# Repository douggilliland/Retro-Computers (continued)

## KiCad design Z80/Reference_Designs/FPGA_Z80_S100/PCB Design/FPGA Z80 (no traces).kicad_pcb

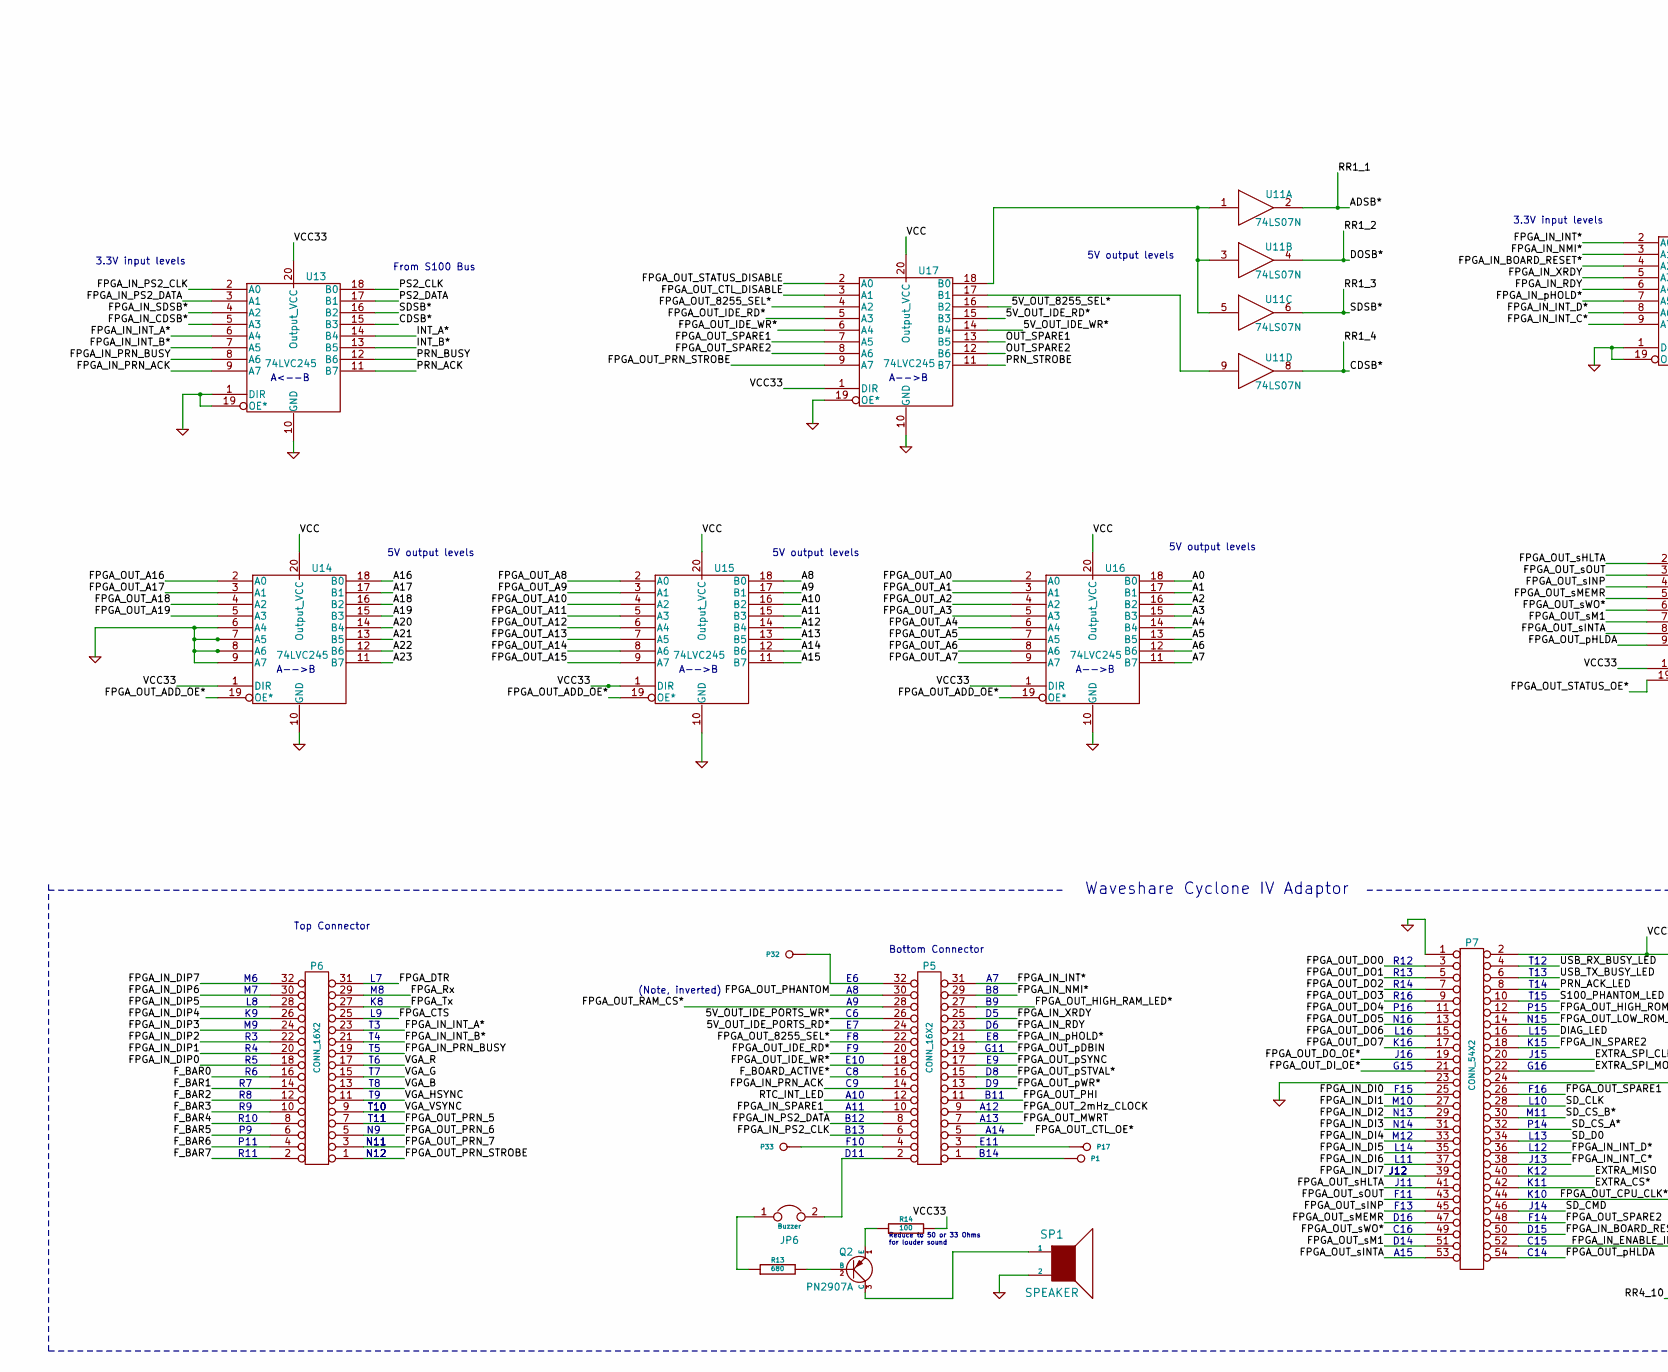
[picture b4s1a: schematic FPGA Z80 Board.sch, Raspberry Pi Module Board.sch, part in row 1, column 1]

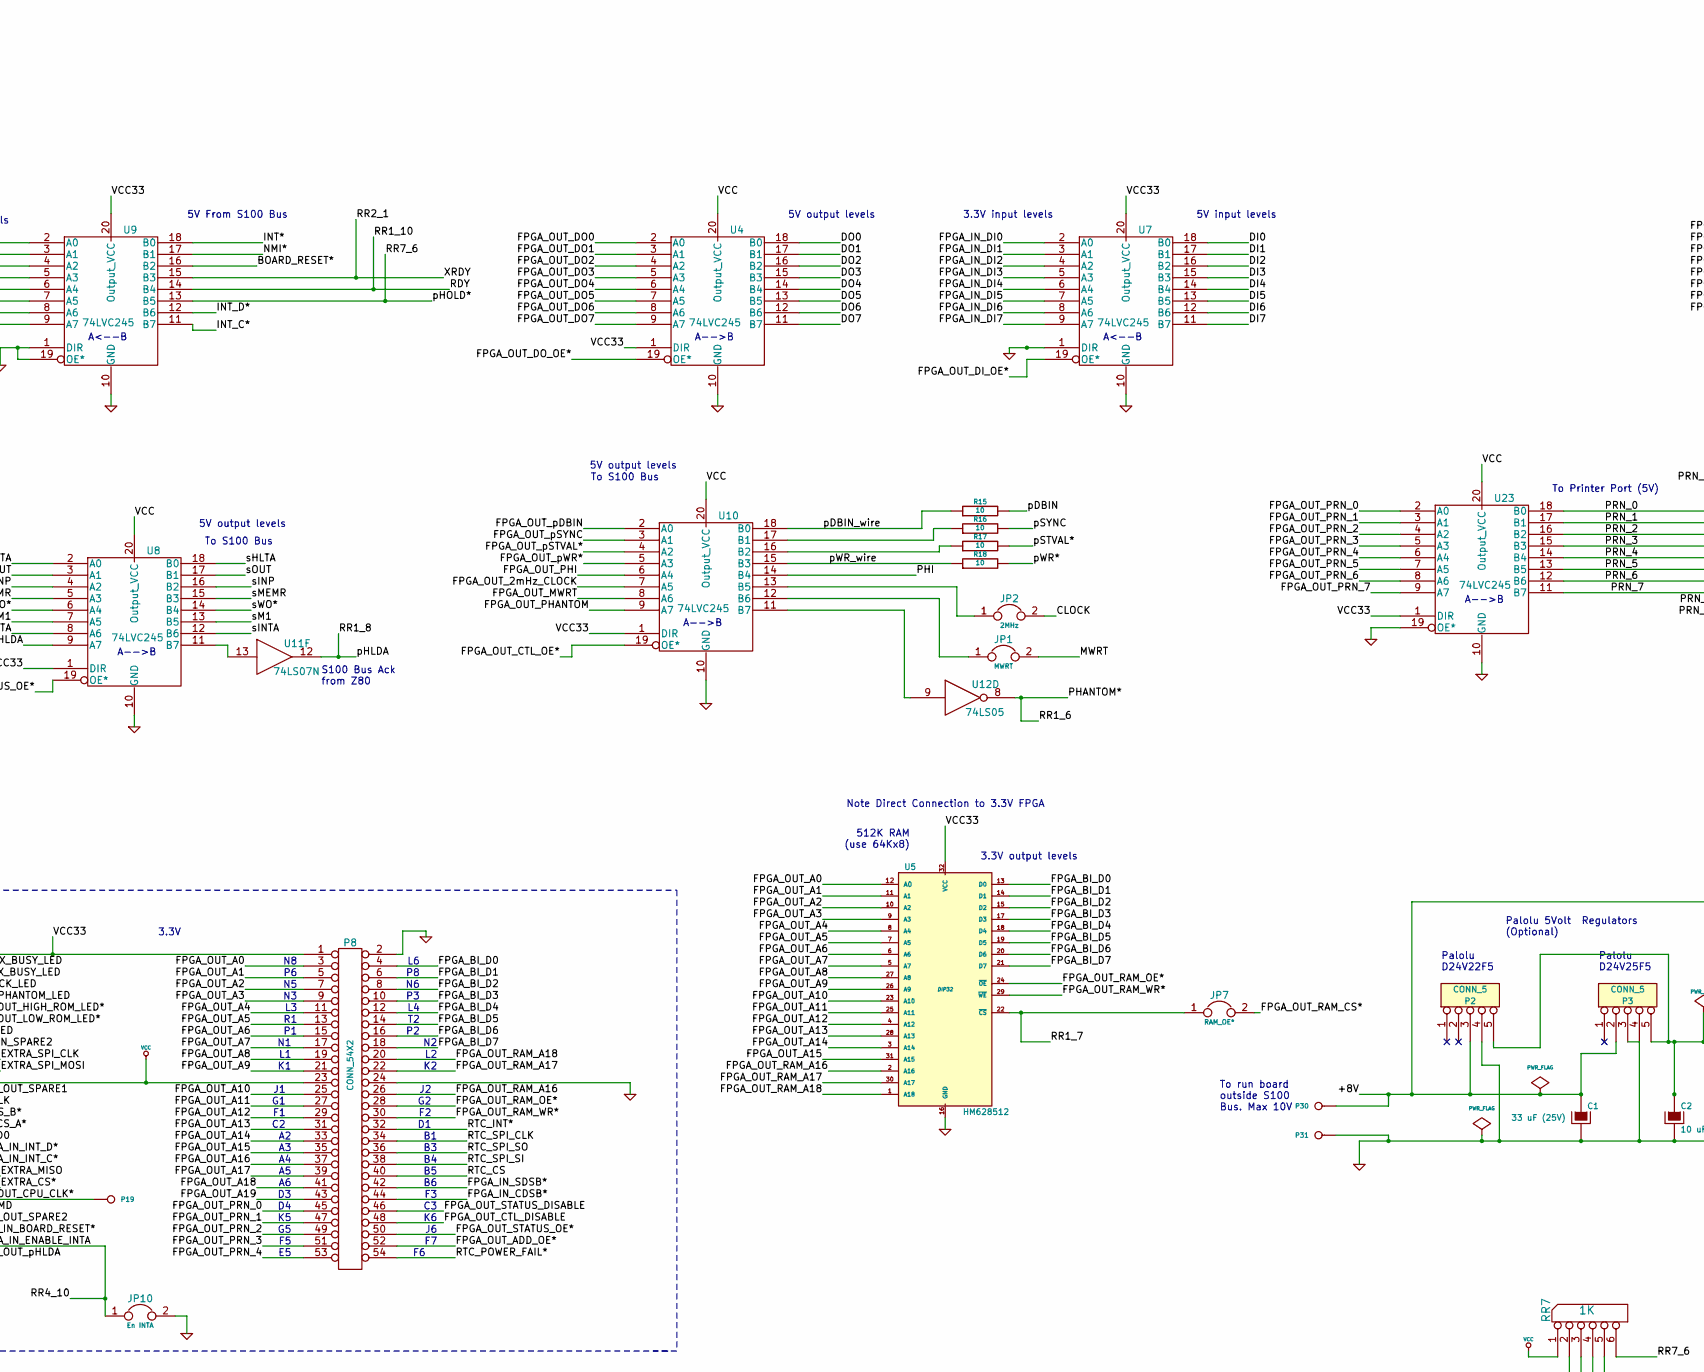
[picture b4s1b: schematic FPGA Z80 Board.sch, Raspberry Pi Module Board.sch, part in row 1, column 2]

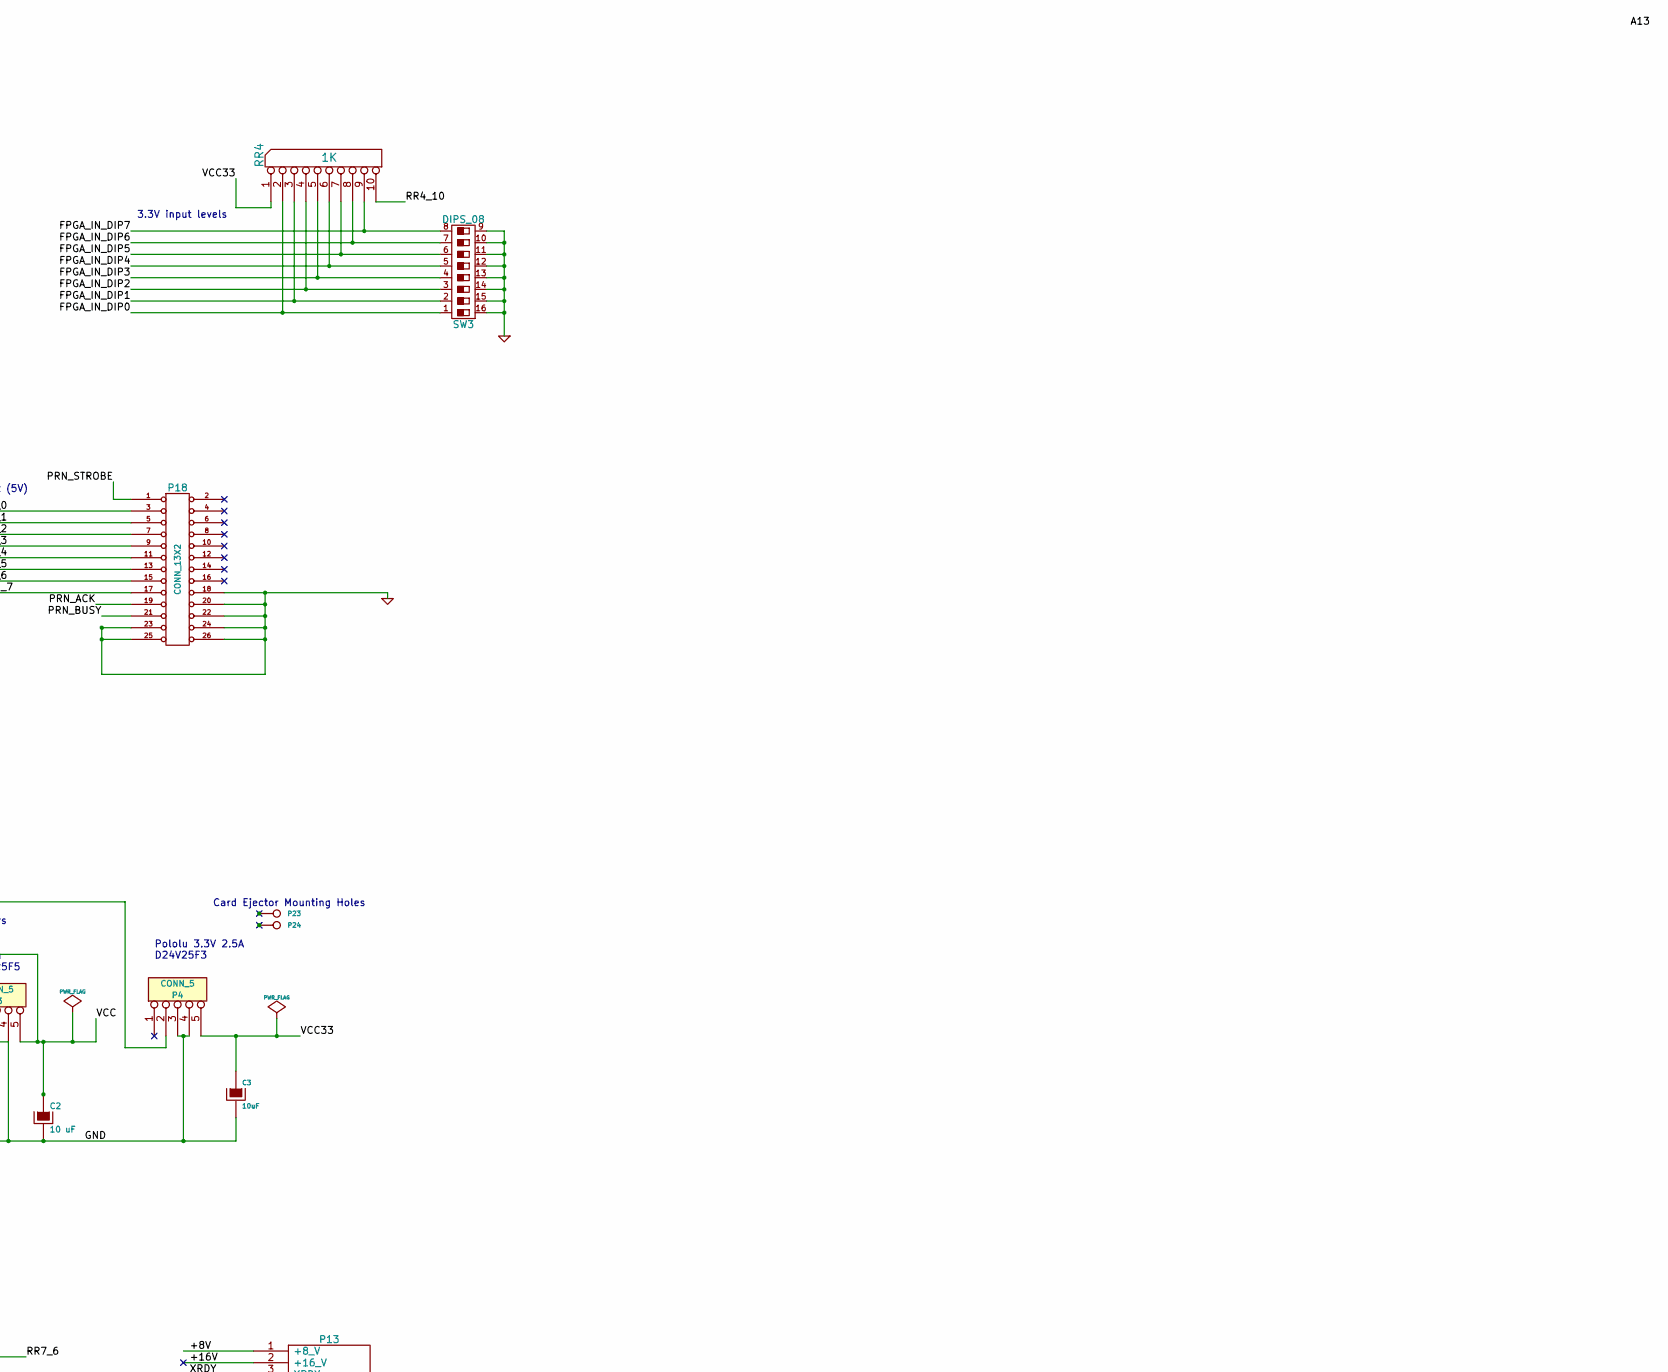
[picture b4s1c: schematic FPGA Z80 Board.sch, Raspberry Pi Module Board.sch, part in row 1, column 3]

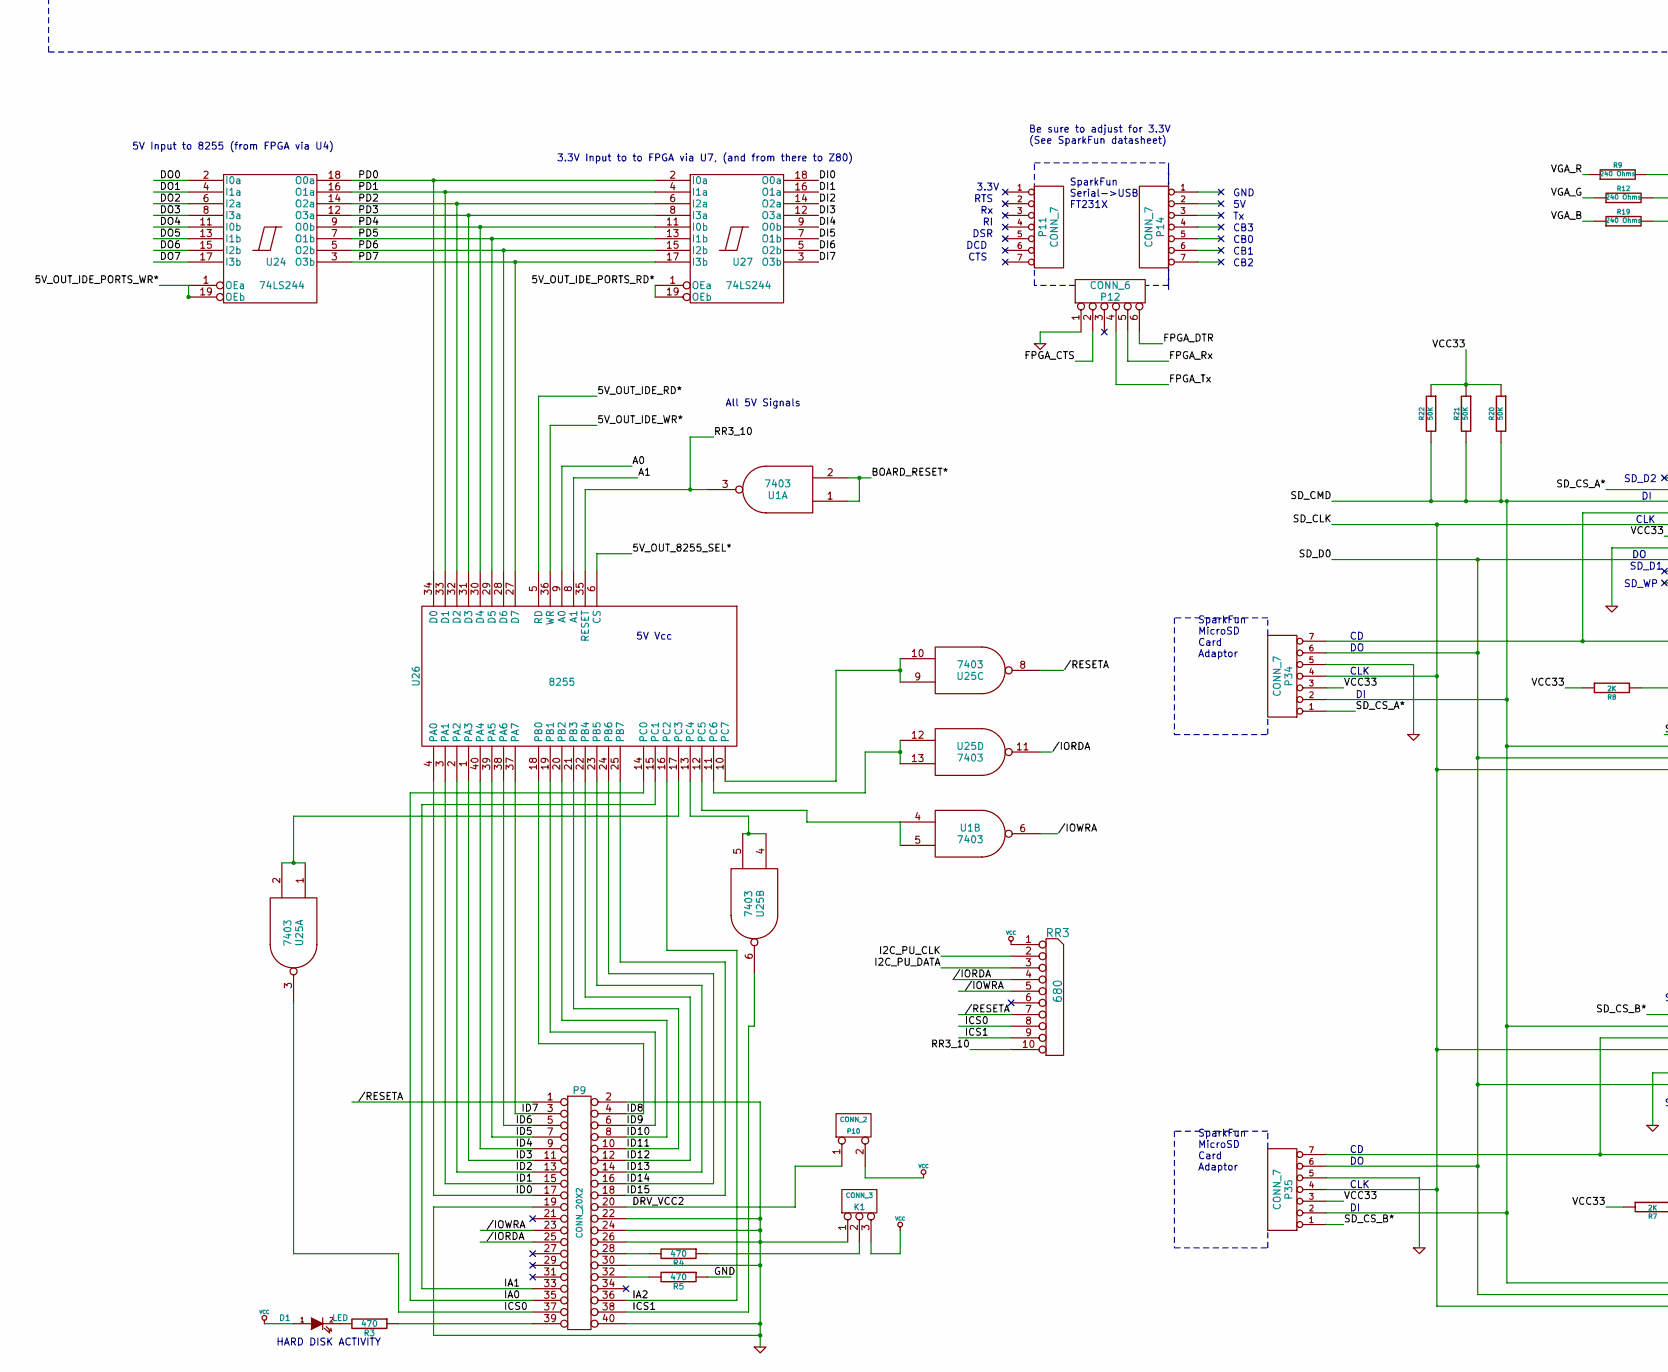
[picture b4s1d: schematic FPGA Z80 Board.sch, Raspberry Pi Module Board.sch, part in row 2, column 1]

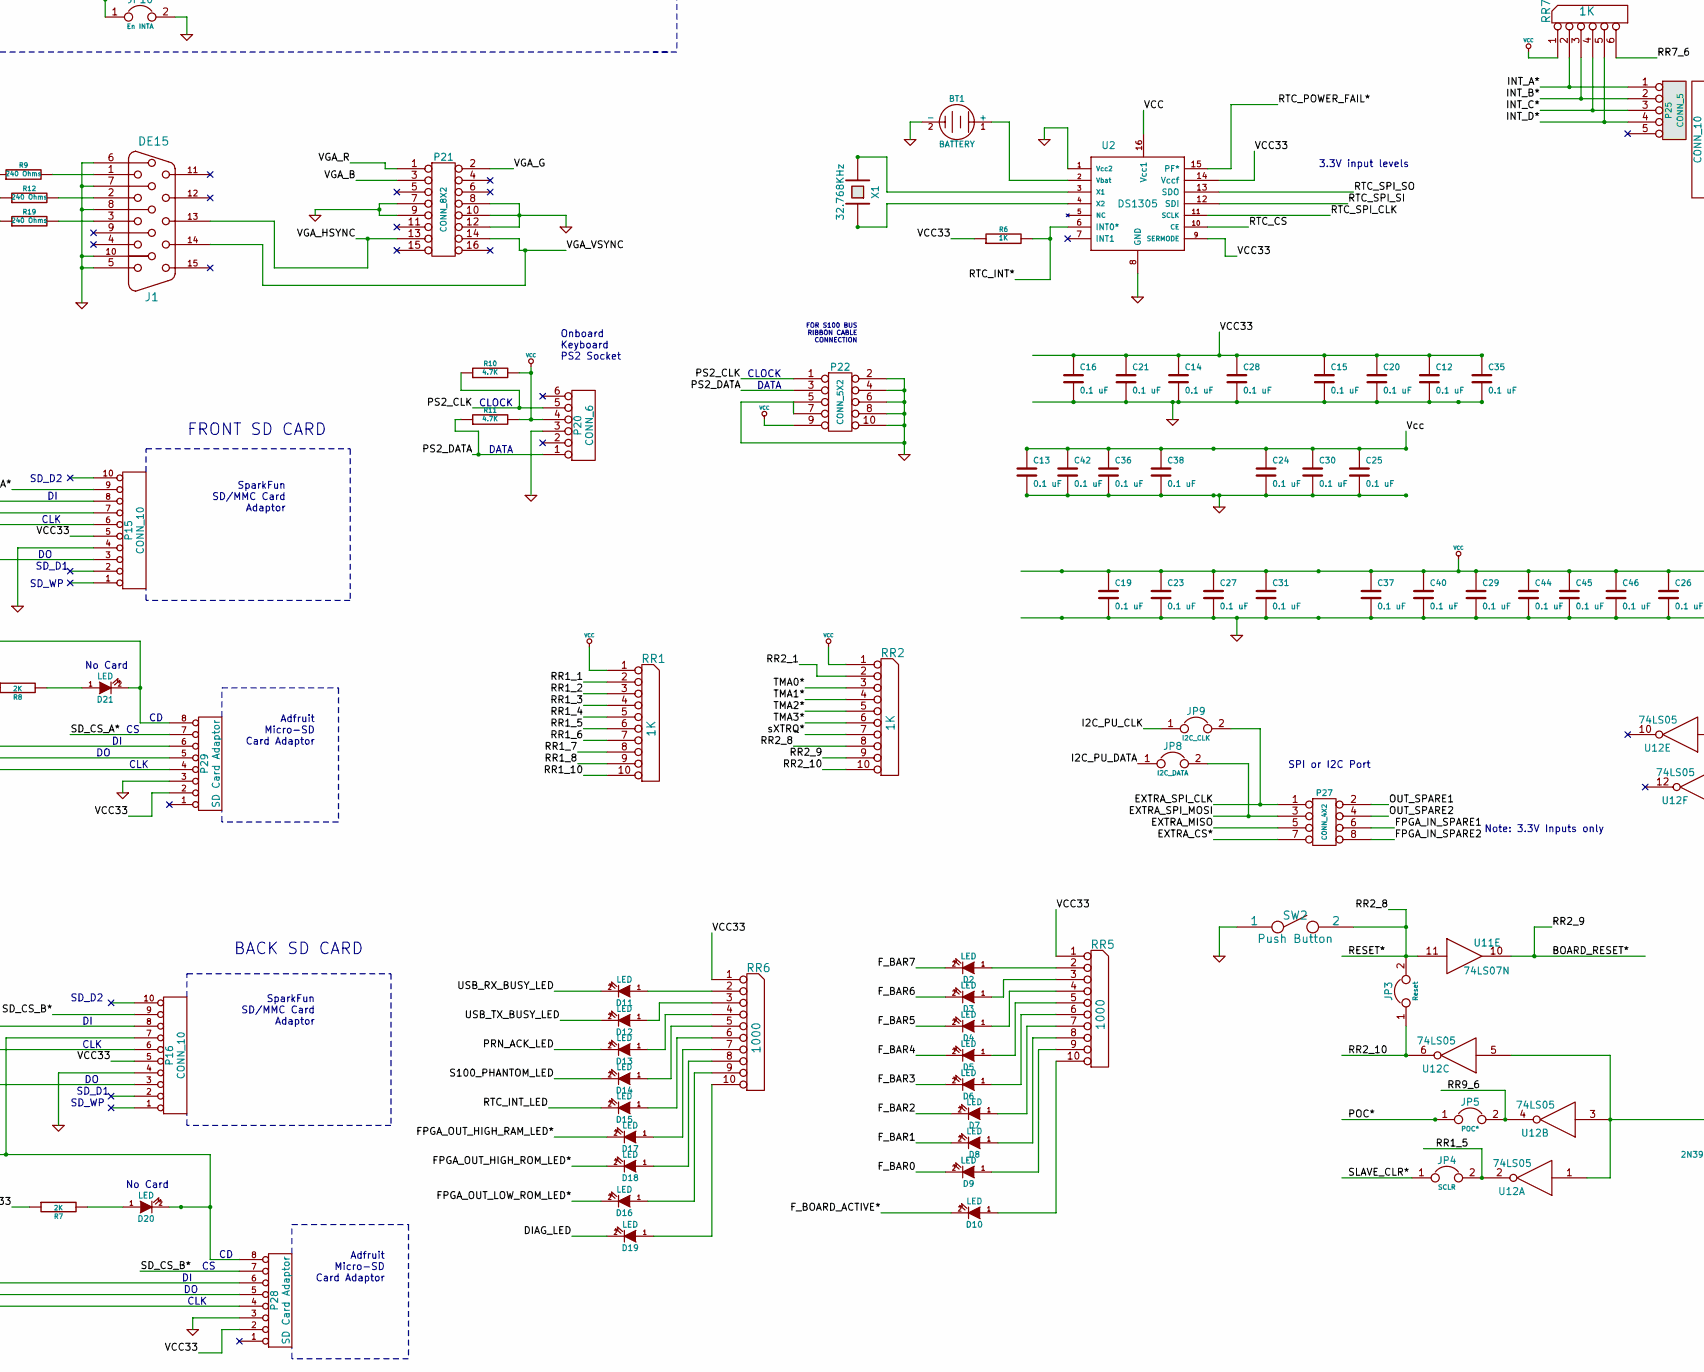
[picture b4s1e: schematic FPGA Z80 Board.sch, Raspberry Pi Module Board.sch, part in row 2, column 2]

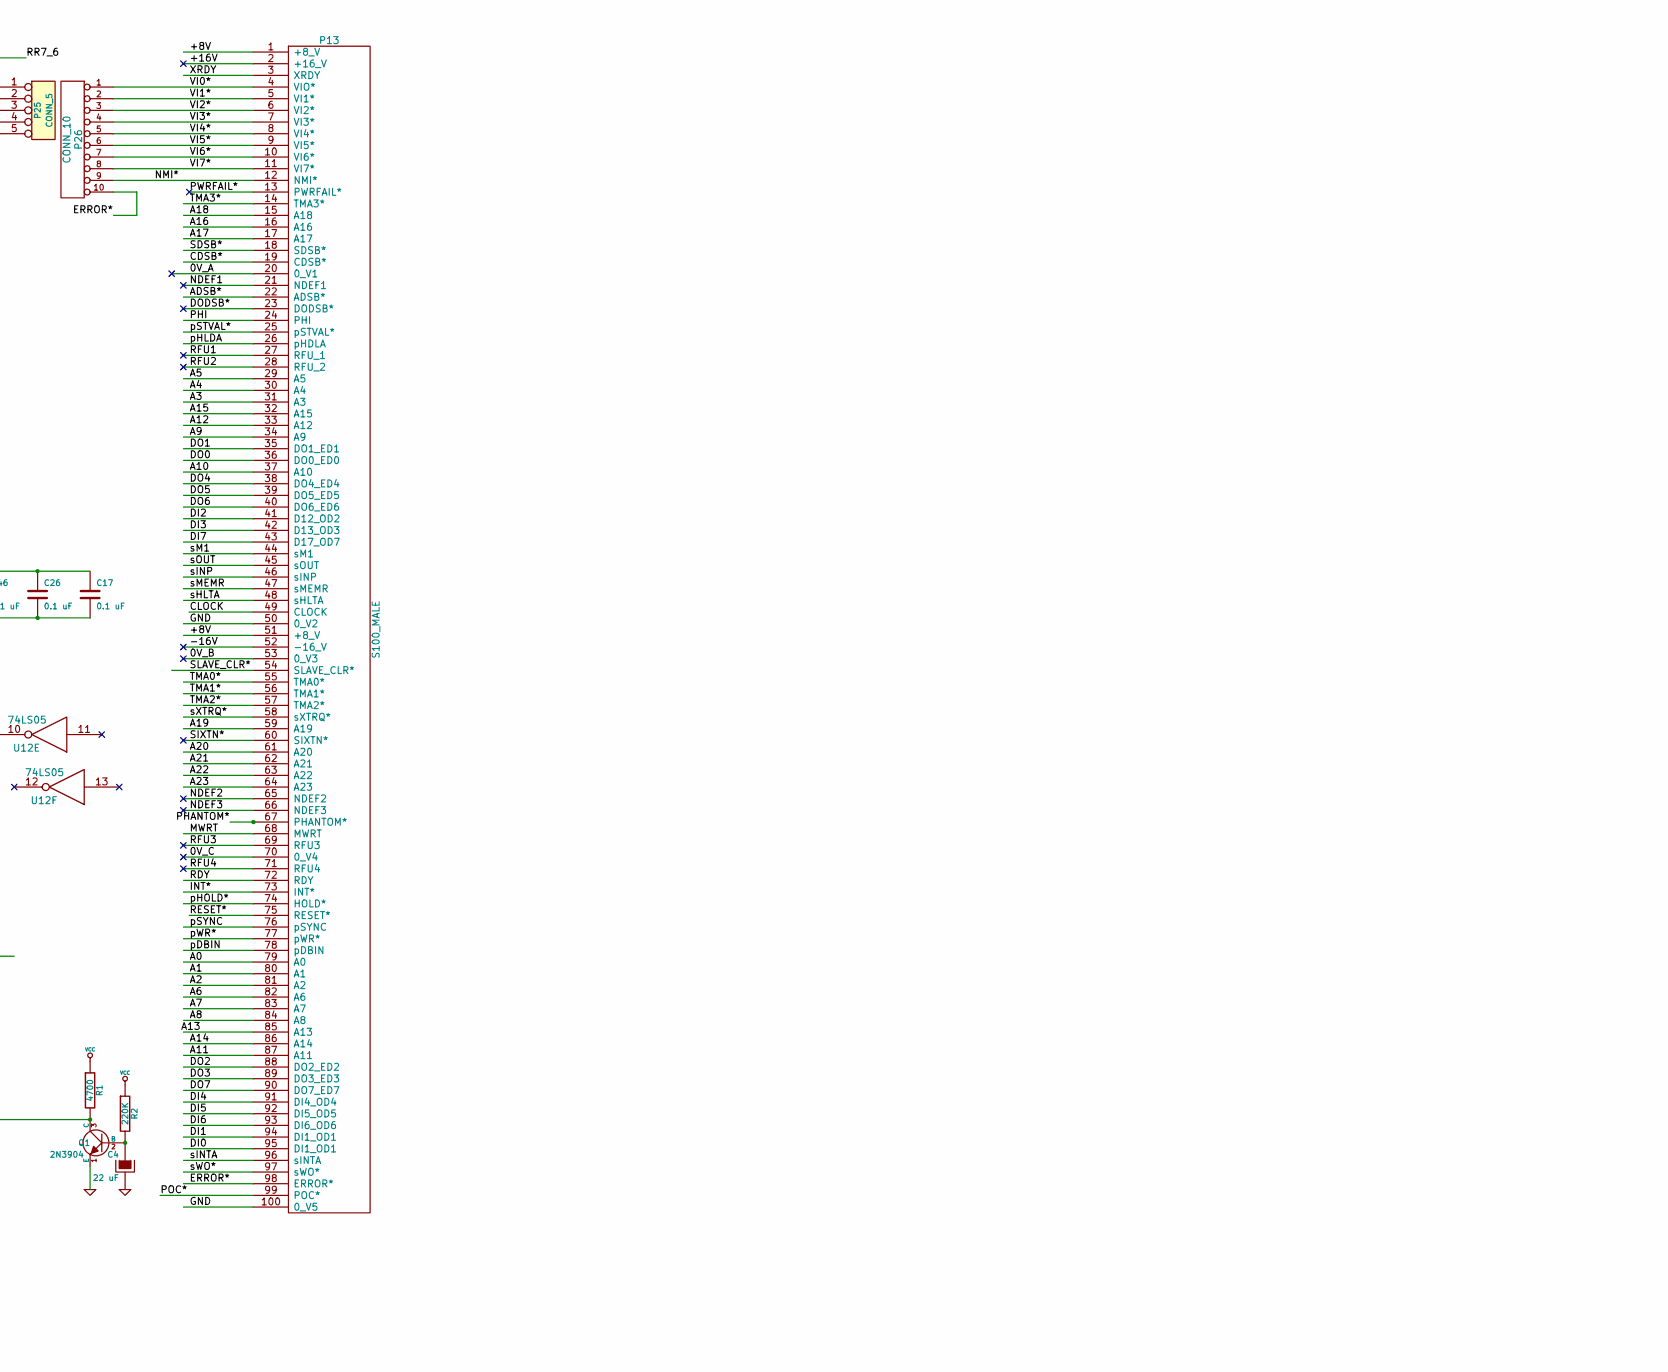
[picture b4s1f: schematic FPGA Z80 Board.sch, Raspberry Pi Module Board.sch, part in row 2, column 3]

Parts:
BT1: BATTERY
C1: 33 uF (25V); C1V5
C2: 10 uF; C1V5
C3: 10uF
C4: 22 uF; C1V5
C12, C13, C14, C15, C16, C17, C19, C20, C21, C23, C24, C25, C26, C27, C28, C29, C30, C31, C35, C36, C37, C38, C40, C42, C44, C45, C46: 0.1 uF; C2
D1: LED; LEDV
D2, D3, D4, D5, D6, D7, D8, D9, D10, D11, D12, D13, D14, D15, D16, D17, D18, D19, D20, D21: LED
J1: DE15
JP1: MWRT; SIL-2
JP2: 2MHz; SIL-2
JP3: Reset; SIL-2
JP4: SCLR; SIL-2
JP5: POC*; SIL-2
JP6: Buzzer; SIL-2
JP7: RAM_OE*; SIL-2
JP8: I2C_DATA; SIL-2
JP9: I2C_CLK; SIL-2
JP10: En INTA; SIL-2
K1: CONN_3
P1, P17, P19, P30, P31: CONN_1
P2, P3, P25: CONN_5
P4: CONN_5
P5, P6: CONN_16X2
P7, P8: CONN_54X2
P9: CONN_20X2; PIN_ARRAY_20X2
P10: CONN_2
P11, P14, P34, P35: CONN_7
P12: CONN_6
P13: S100_MALE
P15, P16, P26: CONN_10
P18: CONN_13X2
P20: CONN_6
P21: CONN_8X2
P22: CONN_5X2; PIN_ARRAY_5x2
P23, P24: CONN_1; 1pin
P27: CONN_4X2
P28, P29: SD Card Adaptor
P32: P32
P33: P33
Q1: 2N3904; TO92-INVERT
Q2: PN2907A
R1: 4700; R3
R2: 220K; R3
R3, R4, R5: 470; R3
R6: 1K
R7, R8: 2K
R9, R12, R19: 240 Ohms
R10, R11: 4.7K
R13: 680
R14: 100
R15, R16, R17, R18: 10
R20, R21, R22: 50K
RR1, RR2, RR4, RR7: 1K
RR3: 680
RR5, RR6: 1000; r_pack9
SP1: SPEAKER
SW2: Push Button
SW3: DIPS_08
U1, U25: 7403; 14dip300
U2: DS1305
U4, U7, U8, U9, U10, U13, U14, U15, U16, U17, U23: 74LVC245
U5: HM628512; DIP32
U11: 74LS07N
U12: 74LS05
U24, U27: 74LS244; 20dip300
U26: 8255; 40dip600
X1: 32.768KHz

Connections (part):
/5V_OUT_8255_SEL*: U17.16 (B2), U26.6 (CS)
/5V_OUT_IDE_PORTS_RD*: P5.24, U27.1 (OEa), U27.19 (OEb)
/5V_OUT_IDE_PORTS_WR*: P5.26, U24.1 (OEa), U24.19 (OEb)
/5V_OUT_IDE_RD*: U17.15 (B3), U26.5 (RD)
/5V_OUT_IDE_WR*: U17.14 (B4), U26.36 (WR)
/+8V: C1.1, P2.3, P3.2, P4.2, P13.1 (+8_V), P13.51 (+8_V), P30.1
//IORDA: P9.25, RR3.4, U25.11
//IOWRA: P9.23, RR3.5, U1.6
//RESETA: P9.1, RR3.7, U25.8
/A0: P13.79 (A0), U16.18 (B0), U26.9 (A0)
/A1: P13.80 (A1), U16.17 (B1), U26.8 (A1)
/A2: P13.81 (A2), U16.16 (B2)
/A3: P13.31 (A3), U16.15 (B3)
/A4: P13.30 (A4), U16.14 (B4)
/A5: P13.29 (A5), U16.13 (B5)
/A6: P13.82 (A6), U16.12 (B6)
/A7: P13.83 (A7), U16.11 (B7)
/A8: P13.84 (A8), U15.18 (B0)
/A9: P13.34 (A9), U15.17 (B1)
/A10: P13.37 (A10), U15.16 (B2)
/A11: P13.87 (A11), U15.15 (B3)
/A12: P13.33 (A12), U15.14 (B4)
/A13: P13.85 (A13), U15.13 (B5)
/A14: P13.86 (A14), U15.12 (B6)
/A15: P13.32 (A15), U15.11 (B7)
/A16: P13.16 (A16), U14.18 (B0)
/A17: P13.17 (A17), U14.17 (B1)
/A18: P13.15 (A18), U14.16 (B2)
/A19: P13.59 (A19), U14.15 (B3)
/A20: P13.61 (A20), U14.14 (B4)
/A21: P13.62 (A21), U14.13 (B5)
/A22: P13.63 (A22), U14.12 (B6)
/A23: P13.64 (A23), U14.11 (B7)
/ADSB*: P13.22 (ADSB*), RR1.2, U11.2
/BOARD_RESET*: RR2.9, U1.1, U1.2, U9.16 (B2), U11.10
/CDSB*: P13.19 (CDSB*), RR1.5, U11.8, U13.15 (B3)
/CLOCK: JP2.2, P13.49 (CLOCK)
/DI0: P13.95 (DI1_OD1), U7.18 (B0), U27.18 (O0a)
/DI1: P13.94 (DI1_OD1), U7.17 (B1), U27.16 (O1a)
/DI2: P13.41 (D12_OD2), U7.16 (B2), U27.14 (O2a)
/DI3: P13.42 (D13_OD3), U7.15 (B3), U27.12 (O3a)
/DI4: P13.91 (DI4_OD4), U7.14 (B4), U27.9 (O0b)
/DI5: P13.92 (DI5_OD5), U7.13 (B5), U27.7 (O1b)
/DI6: P13.93 (DI6_OD6), U7.12 (B6), U27.5 (O2b)
/DI7: P13.43 (D17_OD7), U7.11 (B7), U27.3 (O3b)
/DIAG_LED: D19.2 (K), P7.16
/DO0: P13.36 (DO0_ED0), U4.18 (B0), U24.2 (I0a)
/DO1: P13.35 (DO1_ED1), U4.17 (B1), U24.4 (I1a)
/DO2: P13.88 (DO2_ED2), U4.16 (B2), U24.6 (I2a)
/DO3: P13.89 (DO3_ED3), U4.15 (B3), U24.8 (I3a)
/DO4: P13.38 (DO4_ED4), U4.14 (B4), U24.11 (I0b)
/DO5: P13.39 (DO5_ED5), U4.13 (B5), U24.13 (I1b)
/DO6: P13.40 (DO6_ED6), U4.12 (B6), U24.15 (I2b)
/DO7: P13.90 (DO7_ED7), U4.11 (B7), U24.17 (I3b)
/DOSB*: RR1.3, U11.4
/DRV_VCC2: P9.20, P10.1
/ERROR*: P13.98 (ERROR*), P26.10
/EXTRA_CS*: P7.42, P27.7
/EXTRA_MISO: P7.40, P27.5
/EXTRA_SPI_CLK: JP9.2, P7.20, P27.1
/EXTRA_SPI_MOSI: JP8.2, P7.22, P27.3
/FPGA_BI_D0: P8.4, U5.13 (D0)
/FPGA_BI_D1: P8.6, U5.14 (D1)
/FPGA_BI_D2: P8.8, U5.15 (D2)
/FPGA_BI_D3: P8.10, U5.17 (D3)
/FPGA_BI_D4: P8.12, U5.18 (D4)
/FPGA_BI_D5: P8.14, U5.19 (D5)
/FPGA_BI_D6: P8.16, U5.20 (D6)
/FPGA_BI_D7: P8.18, U5.21 (D7)
/FPGA_CTS: P6.25, P12.2
/FPGA_DTR: P6.31, P12.6
/FPGA_IN_BOARD_RESET*: P7.50, U9.4 (A2)
/FPGA_IN_CDSB*: P8.44, U13.5 (A3)
/FPGA_IN_DI0: P7.25, U7.2 (A0)
/FPGA_IN_DI1: P7.27, U7.3 (A1)
/FPGA_IN_DI2: P7.29, U7.4 (A2)
/FPGA_IN_DI3: P7.31, U7.5 (A3)
/FPGA_IN_DI4: P7.33, U7.6 (A4)
/FPGA_IN_DI5: P7.35, U7.7 (A5)
/FPGA_IN_DI6: P7.37, U7.8 (A6)
/FPGA_IN_DI7: P7.39, U7.9 (A7)
/FPGA_IN_DIP0: P6.18, RR4.2, SW3.1
/FPGA_IN_DIP1: P6.20, RR4.3, SW3.2
/FPGA_IN_DIP2: P6.22, RR4.4, SW3.3
/FPGA_IN_DIP3: P6.24, RR4.5, SW3.4
/FPGA_IN_DIP4: P6.26, RR4.6, SW3.5
/FPGA_IN_DIP5: P6.28, RR4.7, SW3.6
/FPGA_IN_DIP6: P6.30, RR4.8, SW3.7
/FPGA_IN_DIP7: P6.32, RR4.9, SW3.8
/FPGA_IN_ENABLE_INTA: JP10.1, P7.52, RR4.10
/FPGA_IN_INT*: P5.31, U9.2 (A0)
/FPGA_IN_INT_A*: P6.23, U13.6 (A4)
/FPGA_IN_INT_B*: P6.21, U13.7 (A5)
/FPGA_IN_INT_C*: P7.38, U9.9 (A7)
/FPGA_IN_INT_D*: P7.36, U9.8 (A6)
/FPGA_IN_NMI*: P5.29, U9.3 (A1)
/FPGA_IN_PRN_ACK: P5.14, U13.9 (A7)
/FPGA_IN_PRN_BUSY: P6.19, U13.8 (A6)
/FPGA_IN_PS2_CLK: P5.6, U13.2 (A0)
/FPGA_IN_PS2_DATA: P5.8, U13.3 (A1)
/FPGA_IN_RDY: P5.23, U9.6 (A4)
/FPGA_IN_SDSB*: P8.42, U13.4 (A2)
/FPGA_IN_SPARE1: P5.10, P27.6
/FPGA_IN_SPARE2: P7.18, P27.8
/FPGA_IN_XRDY: P5.25, U9.5 (A3)
/FPGA_IN_pHOLD*: P5.21, U9.7 (A5)
/FPGA_OUT_2mHz_CLOCK: P5.9, U10.7 (A5)
/FPGA_OUT_8255_SEL*: P5.22, U17.4 (A2)
/FPGA_OUT_A0: P8.3, U5.12 (A0), U16.2 (A0)
/FPGA_OUT_A1: P8.5, U5.11 (A1), U16.3 (A1)
/FPGA_OUT_A2: P8.7, U5.10 (A2), U16.4 (A2)
/FPGA_OUT_A3: P8.9, U5.9 (A3), U16.5 (A3)
/FPGA_OUT_A4: P8.11, U5.8 (A4), U16.6 (A4)
/FPGA_OUT_A5: P8.13, U5.7 (A5), U16.7 (A5)
/FPGA_OUT_A6: P8.15, U5.6 (A6), U16.8 (A6)
/FPGA_OUT_A7: P8.17, U5.5 (A7), U16.9 (A7)
/FPGA_OUT_A8: P8.19, U5.27 (A8), U15.2 (A0)
/FPGA_OUT_A9: P8.21, U5.26 (A9), U15.3 (A1)
/FPGA_OUT_A10: P8.25, U5.23 (A10), U15.4 (A2)
/FPGA_OUT_A11: P8.27, U5.25 (A11), U15.5 (A3)
/FPGA_OUT_A12: P8.29, U5.4 (A12), U15.6 (A4)
/FPGA_OUT_A13: P8.31, U5.28 (A13), U15.7 (A5)
/FPGA_OUT_A14: P8.33, U5.3 (A14), U15.8 (A6)
/FPGA_OUT_A15: P8.35, U5.31 (A15), U15.9 (A7)
/FPGA_OUT_A16: P8.37, U14.2 (A0)
/FPGA_OUT_A17: P8.39, U14.3 (A1)
/FPGA_OUT_A18: P8.41, U14.4 (A2)
/FPGA_OUT_A19: P8.43, U14.5 (A3)
/FPGA_OUT_ADD_OE*: P8.52, U14.19 (OE*), U15.19 (OE*), U16.19 (OE*)
/FPGA_OUT_CPU_CLK*: P7.44, P19.1
/FPGA_OUT_CTL_DISABLE: P8.48, U17.3 (A1)
/FPGA_OUT_CTL_OE*: P5.5, U10.19 (OE*)
/FPGA_OUT_DI_OE*: P7.21, U7.19 (OE*)
/FPGA_OUT_DO0: P7.3, U4.2 (A0)
/FPGA_OUT_DO1: P7.5, U4.3 (A1)
/FPGA_OUT_DO2: P7.7, U4.4 (A2)
/FPGA_OUT_DO3: P7.9, U4.5 (A3)
/FPGA_OUT_DO4: P7.11, U4.6 (A4)
/FPGA_OUT_DO5: P7.13, U4.7 (A5)
/FPGA_OUT_DO6: P7.15, U4.8 (A6)
/FPGA_OUT_DO7: P7.17, U4.9 (A7)
/FPGA_OUT_DO_OE*: P7.19, U4.19 (OE*)
/FPGA_OUT_HIGH_RAM_LED*: D17.2 (K), P5.27
/FPGA_OUT_HIGH_ROM_LED*: D18.2 (K), P7.12
/FPGA_OUT_IDE_RD*: P5.20, U17.5 (A3)
/FPGA_OUT_IDE_WR*: P5.18, U17.6 (A4)
/FPGA_OUT_LOW_ROM_LED*: D16.2 (K), P7.14
/FPGA_OUT_MWRT: P5.7, U10.8 (A6)
/FPGA_OUT_PHANTOM: P5.30, U10.9 (A7)
/FPGA_OUT_PHI: P5.11, U10.6 (A4)
/FPGA_OUT_PRN_0: P8.45, U23.2 (A0)
/FPGA_OUT_PRN_1: P8.47, U23.3 (A1)
/FPGA_OUT_PRN_2: P8.49, U23.4 (A2)
/FPGA_OUT_PRN_3: P8.51, U23.5 (A3)
/FPGA_OUT_PRN_4: P8.53, U23.6 (A4)
/FPGA_OUT_PRN_5: P6.7, U23.7 (A5)
/FPGA_OUT_PRN_6: P6.5, U23.8 (A6)
/FPGA_OUT_PRN_7: P6.3, U23.9 (A7)
/FPGA_OUT_PRN_STROBE: P6.1, U17.9 (A7)
/FPGA_OUT_RAM_A16: P8.26, U5.2 (A16)
/FPGA_OUT_RAM_A17: P8.22, U5.30 (A17)
/FPGA_OUT_RAM_A18: P8.20, U5.1 (A18)
/FPGA_OUT_RAM_CS*: JP7.2, P5.28
/FPGA_OUT_RAM_OE*: P8.28, U5.24 (~OE)
/FPGA_OUT_RAM_WR*: P8.30, U5.29 (~WE)
/FPGA_OUT_SPARE1: P7.26, U17.7 (A5)
/FPGA_OUT_SPARE2: P7.48, U17.8 (A6)
/FPGA_OUT_STATUS_DISABLE: P8.46, U17.2 (A0)
/FPGA_OUT_STATUS_OE*: P8.50, U8.19 (OE*)
/FPGA_OUT_pDBIN: P5.19, U10.2 (A0)
/FPGA_OUT_pHLDA: P7.54, U8.9 (A7)
/FPGA_OUT_pSTVAL*: P5.15, U10.4 (A2)
/FPGA_OUT_pSYNC: P5.17, U10.3 (A1)
/FPGA_OUT_pWR*: P5.13, U10.5 (A3)
/FPGA_OUT_sHLTA: P7.41, U8.2 (A0)
/FPGA_OUT_sINP: P7.45, U8.4 (A2)
/FPGA_OUT_sINTA: P7.53, U8.8 (A6)
/FPGA_OUT_sM1: P7.51, U8.7 (A5)
/FPGA_OUT_sMEMR: P7.47, U8.5 (A3)
/FPGA_OUT_sOUT: P7.43, U8.3 (A1)
/FPGA_OUT_sWO*: P7.49, U8.6 (A4)
/FPGA_Rx: P6.29, P12.5
/FPGA_Tx: P6.27, P12.4
/F_BAR0: D9.2 (K), P6.16
/F_BAR1: D8.2 (K), P6.14
/F_BAR2: D7.2 (K), P6.12
/F_BAR3: D6.2 (K), P6.10
/F_BAR4: D5.2 (K), P6.8
/F_BAR5: D4.2 (K), P6.6
/F_BAR6: D3.2 (K), P6.4
/F_BAR7: D2.2 (K), P6.2
/F_BOARD_ACTIVE*: D10.2 (K), P5.16
/I2C_PU_CLK: JP9.1, RR3.2
/I2C_PU_DATA: JP8.1, RR3.3
/IA0: P9.35, U26.14 (PC0)
/IA1: P9.33, U26.15 (PC1)
/IA2: P9.36, U26.16 (PC2)
/ICS0: P9.37, RR3.8, U25.3
/ICS1: P9.38, RR3.9, U25.6
/ID0: P9.17, U26.4 (PA0)
/ID1: P9.15, U26.3 (PA1)
/ID2: P9.13, U26.2 (PA2)
/ID3: P9.11, U26.1 (PA3)
/ID4: P9.9, U26.40 (PA4)
/ID5: P9.7, U26.39 (PA5)
/ID6: P9.5, U26.38 (PA6)
/ID7: P9.3, U26.37 (PA7)
/ID8: P9.4, U26.18 (PB0)
/ID9: P9.6, U26.19 (PB1)
/ID10: P9.8, U26.20 (PB2)
/ID11: P9.10, U26.21 (PB3)
/ID12: P9.12, U26.22 (PB4)
/ID13: P9.14, U26.23 (PB5)
/ID14: P9.16, U26.24 (PB6)
/ID15: P9.18, U26.25 (PB7)
/INT*: P13.73 (INT*), U9.18 (B0)
/INT_A*: P25.1, RR7.2, U13.14 (B4)
/INT_B*: P25.2, RR7.3, U13.13 (B5)
/INT_C*: P25.3, RR7.4, U9.11 (B7)
/INT_D*: P25.4, RR7.5, U9.12 (B6)
/MWRT: JP1.2, P13.68 (MWRT)
/NMI*: P13.12 (NMI*), P26.9, U9.17 (B1)
/OUT_SPARE1: P27.2, U17.13 (B5)
/OUT_SPARE2: P27.4, U17.12 (B6)
/PD0: U24.18 (O0a), U26.34 (D0), U27.2 (I0a)
/PD1: U24.16 (O1a), U26.33 (D1), U27.4 (I1a)
/PD2: U24.14 (O2a), U26.32 (D2), U27.6 (I2a)
/PD3: U24.12 (O3a), U26.31 (D3), U27.8 (I3a)
/PD4: U24.9 (O0b), U26.30 (D4), U27.11 (I0b)
/PD5: U24.7 (O1b), U26.29 (D5), U27.13 (I1b)
/PD6: U24.5 (O2b), U26.28 (D6), U27.15 (I2b)
/PD7: U24.3 (O3b), U26.27 (D7), U27.17 (I3b)
/PHANTOM*: P13.67 (PHANTOM*), RR1.7, U12.8
/PHI: P13.24 (PHI), U10.14 (B4)
/POC*: JP5.1, P13.99 (POC*)
/PRN_0: P18.3, U23.18 (B0)
/PRN_1: P18.5, U23.17 (B1)
/PRN_2: P18.7, U23.16 (B2)
/PRN_3: P18.9, U23.15 (B3)
/PRN_4: P18.11, U23.14 (B4)
/PRN_5: P18.13, U23.13 (B5)
/PRN_6: P18.15, U23.12 (B6)
/PRN_7: P18.17, U23.11 (B7)
/PRN_ACK: P18.19, U13.11 (B7)
/PRN_ACK_LED: D13.2 (K), P7.8
/PRN_BUSY: P18.21, U13.12 (B6)
/PRN_STROBE: P18.1, U17.11 (B7)
/PS2_CLK: P20.5, P22.1, R10.1, U13.18 (B0)
/PS2_DATA: P20.1, P22.3, R11.1, U13.17 (B1)
/RDY: P13.72 (RDY), RR1.10, U9.14 (B4)
/RESET*: JP3.2, P13.75 (RESET*), RR2.8, SW2.2, U11.11
/RR1_3: P13.18 (SDSB*), RR1.4, U11.6, U13.16 (B2)
/RR1_5: JP4.2, RR1.6, U12.2
/RR1_7: JP7.1, RR1.8, U5.22 (~CS)
/RR1_8: P13.26 (pHDLA), RR1.9, U11.12
/RR2_1: P13.3 (XRDY), RR2.2, U9.15 (B3)
/RR2_10: JP3.1, RR2.10, U12.6
/RR3_10: RR3.10, U1.3, U26.35 (RESET)
/RR7_6: P13.74 (HOLD*), RR7.6, U9.13 (B5)
/RR9_6: JP5.2, U12.4
/RTC_CS: P8.40, U2.10 (CE)
/RTC_INT*: P8.32, R6.2, U2.6 (INT0*)
/RTC_INT_LED: D15.2 (K), P5.12
/RTC_POWER_FAIL*: P8.54, U2.15 (PF*)
/RTC_SPI_CLK: P8.34, U2.11 (SCLK)
/RTC_SPI_SI: P8.38, U2.12 (SDI)
/RTC_SPI_SO: P8.36, U2.13 (SDO)
/S100_PHANTOM_LED: D14.2 (K), P7.10
/SD_CLK: P7.28, P15.6, P16.6, P28.4, P29.4, P34.4, P35.4
/SD_CMD: P7.46, P15.8, P16.8, P28.6, P29.6, P34.2, P35.2, R20.2, R21.2, R22.2
/SD_CS_A*: P7.32, P15.9, P29.7, P34.1
/SD_CS_B*: P7.30, P16.9, P28.7, P35.1
/SD_D0: P7.34, P15.3, P16.3, P28.5, P29.5, P34.6, P35.6
/SLAVE_CLR*: JP4.1, P13.54 (SLAVE_CLR*)
/TMA0*: P13.55 (TMA0*), RR2.3
/TMA1*: P13.56 (TMA1*), RR2.4
/TMA2*: P13.57 (TMA2*), RR2.5
/TMA3*: P13.14 (TMA3*), RR2.6
/USB_RX_BUSY_LED: D11.2 (K), P7.4
/USB_TX_BUSY_LED: D12.2 (K), P7.6
/VCC33: C3.1, C12.1, C14.1, C15.1, C16.1, C20.1, C21.1, C28.1, C35.1, P4.5, P7.2, P8.1, P15.5, P16.5, P28.2, P29.2, P34.3, P35.3, R6.1, R7.1, R8.1, R14.2, R20.1, R21.1, R22.1, RR4.1 (COM), RR5.1 (COM), RR6.1 (COM), U2.9 (SERMODE), U2.14 (Vccf), U4.1 (DIR), U5.32 (VCC), U7.20 (Output_VCC), U8.1 (DIR), U9.20 (Output_VCC), U10.1 (DIR), U13.20 (Output_VCC), U14.1 (DIR), U15.1 (DIR), U16.1 (DIR), U17.1 (DIR), U23.1 (DIR)
/VGA_B: P6.13, P21.3, R19.1
/VGA_G: P6.15, P21.2, R12.1
/VGA_HSYNC: J1.13, P6.11, P21.13
/VGA_R: P6.17, P21.1, R9.1
/VGA_VSYNC: J1.14, P6.9, P21.14
/VI0*: P13.4 (VIO*), P26.1
/VI1*: P13.5 (VI1*), P26.2
/VI2*: P13.6 (VI2*), P26.3
/VI3*: P13.7 (VI3*), P26.4
/VI4*: P13.8 (VI4*), P26.5
/VI5*: P13.9 (VI5*), P26.6
/VI6*: P13.10 (VI6*), P26.7
/VI7*: P13.11 (VI7*), P26.8
/pDBIN: P13.78 (pDBIN), R15.2
/pDBIN_wire: R15.1, U10.18 (B0)
/pSTVAL*: P13.25 (pSTVAL*), R17.2
/pSYNC: P13.76 (pSYNC), R16.2
/pWR*: P13.77 (pWR*), R18.2
/pWR_wire: R18.1, U10.15 (B3)
/sHLTA: P13.48 (sHLTA), U8.18 (B0)
/sINP: P13.46 (sINP), U8.16 (B2)
/sINTA: P13.96 (sINTA), U8.12 (B6)
/sM1: P13.44 (sM1), U8.13 (B5)
/sMEMR: P13.47 (sMEMR), U8.15 (B3)
/sOUT: P13.45 (sOUT), U8.17 (B1)
/sWO*: P13.97 (sWO*), U8.14 (B4)
/sXTRQ*: P13.58 (sXTRQ*), RR2.7
GND: BT1.2 (-), C1.2, C2.2, C3.2, C4.2, C12.2, C13.2, C14.2, C15.2, C16.2, C17.2, C19.2, C20.2, C21.2, C23.2, C24.2, C25.2, C26.2, C27.2, C28.2, C29.2, C30.2, C31.2, C35.2, C36.2, C37.2, C38.2, C40.2, C42.2, C44.2, C45.2, C46.2, J1.5, J1.6, J1.7, J1.8, J1.10, JP10.2, K1.1, P2.4, P3.3, P3.4, P4.3, P4.4, P7.1, P7.23, P8.2, P8.24, P9.2, P9.19, P9.22, P9.24, P9.26, P9.30, P9.40, P12.1, P13.50 (0_V2), P13.100 (0_V5), P15.4, P16.4, P18.18, P18.20, P18.22, P18.23, P18.24 (P20), P18.25 (P24), P18.26 (P22), P20.3, P21.7, P21.8, P21.9, P21.10, P21.12, P22.2, P22.4, P22.5, P22.6, P22.7, P22.8, P22.10, P28.3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
unnamed: U11.9, U17.17 (B1)
unnamed: P5.3, P17.1
unnamed: P1.1, P5.1
unnamed: P9.28, R4.2
unnamed: P9.39, R3.1
unnamed: U25.1, U25.2, U26.17 (PC3)
unnamed: U25.4, U25.5, U26.13 (PC4)
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
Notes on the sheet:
Waveshare Cyclone IV Adaptor
3.3V
T12
T13
T14
T15
P15
N15
L15
K15
J15
G16
F16
L10
M11
P14
L13
L12
J13
K12
K11
K10
J14
F14
D15
C15
C14
R12
R13
R14
R16
P16
N16
L16
K16
J16
G15
F15
M10
N13

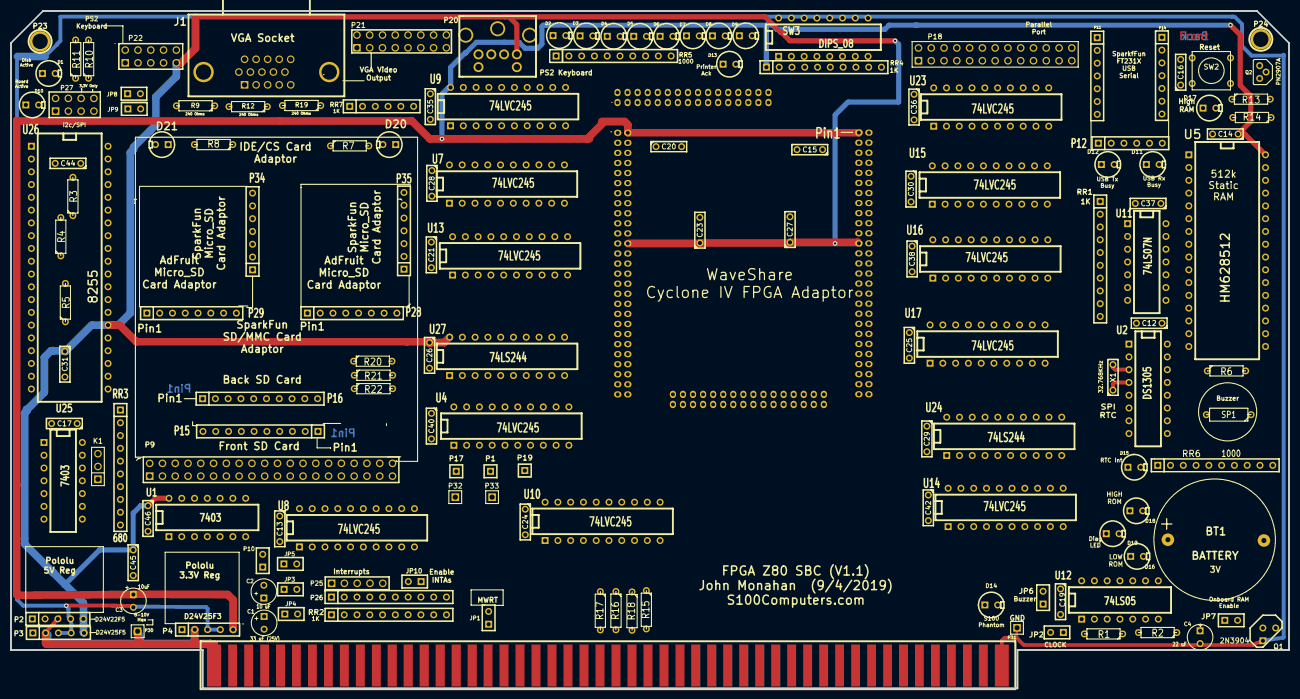
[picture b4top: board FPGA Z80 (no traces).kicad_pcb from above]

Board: 2 copper layers, 254.0 x 134.6 mm, 155 parts (0 on the bottom side), 367 nets.
